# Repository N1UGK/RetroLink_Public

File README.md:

# RetroLink (POTS Telephone Internet Interface)

RetroLink connects a standard POTS (Plain Old Telephone Service) analog telephone to the Internet over Wi-Fi, allowing peer-to-peer calling between devices and retro telephony interfacing.  The RetroLink is intended for private telephone networks in the same building, campus, or even across the globe.  It will not require subscription fees or a third party "app" or platform to use.  The idea came from my daughter (who is 6) asking for a phone to call her friends.  This device can be configured for connecting a close circle of friends or family and using their chosen "phone number" to dial and connect to them.  Any standard "retro" telephone can be plugged into the RetroLink.

## Overview

RetroLink provides a complete, self-contained telephone line interface for real analog telephones (both rotary and DTMF touch-tone). It generates real ringing voltages, provides line battery feed, detects off-hook and on-hook states, digitizes 2-wire voice audio with hardware codecs, and streams bidirectional voice data over Wi-Fi.

## Key Features

- **True POTS Line Interface**: Powered by the **Silvertel Ag1170-S5** SLIC with an onboard DC/DC converter generating -48V loop battery and 65Vrms ringing directly from a 5V supply.
- **Hardware Voice Codec**: **Texas Instruments TLV320AIC1110** providing 8 kHz PCM sampling, companded G.711 µ-law encoding, digital PGA gain control, and programmable sidetone.
- **Microcontroller**: **Raspberry Pi Pico 2 W** (RP2350 with dual ARM Cortex-M33 / Hazard3 RISC-V cores and onboard CYW43 Wi-Fi).
- **Dual-Core Architecture**:
  - **Core 0**: Real-time audio engine with DMA/PIO double buffering, low-latency audio packetization, and SLIC line supervision (hook switch debounce & ring cadence).
  - **Core 1**: CYW43 Wi-Fi stack, lwIP networking, VoIP stream/control protocol, web status interface, and OLED display navigation.
- **User Interface**:
  - 128x64 SSD1306 OLED display via I2C (0x3C)
  - 4-button tactile keypad (Up, Down, OK, Back) via MAX7329 GPIO expander (0x3A)
  - 7 Status LEDs (Off-Hook, MicroSD, Voice Mail, Ringing, Connected, Wi-Fi Link, Error) via MAX7329 (0x38)
- **Local Storage & USB**:
  - MicroSD card slot over SPI0 with FatFS for address books, call logs, and voicemail storage.
  - TinyUSB USB Mass Storage support for mounting the SD card on a PC or Mac.
- **Web Dashboard & Control**:
  - Embedded HTTP server for real-time OLED screen viewing, virtual button control, device status, and network configuration.
- **Secure Firmware Updates**:
  - Dedicated 64 KB custom bootloader with OTP key verification and drag-and-drop UF2 updates over USB.

## Hardware Specifications

| Component | Specification |
|---|---|
| Microcontroller | Raspberry Pi Pico 2 W (RP2350 @ 150MHz) |
| SLIC Module | Silvertel Ag1170-S5 (5V, 600Ω 2-wire impedance) |
| Ring Generator | Onboard Ag1170 ringing (65Vrms @ 20Hz, REN 3 capable) |
| Voice Codec | TI TLV320AIC1110 (PCM / G.711 µ-law, 8 kHz) |
| Display | 0.96" 128x64 I2C OLED (0x3C) |
| I/O Expanders | 2x MAX7329 I2C Expanders (0x38, 0x3A) |
| Power Supply | Single 18650 Li-Ion Cell with BQ24090 Charger & MCP1642B 5V Boost |
| Connector | Standard RJ-11 6P4C Modular Phone Jack |

## Firmware Updates

To update the firmware:
1. Place RetroLink into bootloader mode via the OLED menu: `Settings -> Update Firmware`, or hold the bootsel/startup button combo on power-up.
2. Connect RetroLink to your computer via USB. A mass-storage drive named `RETROLINK` will appear.
3. Drag and drop the latest release `.uf2` file from the `Firmware/` folder onto the drive.
4. The bootloader will verify and flash the image, then automatically reboot into the new firmware.

## Repository Structure

- `Firmware/`: Official firmware release binaries (`.uf2`) and release notes.
- `Hardware/`: 3D CAD STEP models, schematics, and mechanical design files.
- `Documentation/`: User guides, application notes, and reference manuals.
>>>>>>> b99fa2f (Initial commit for RetroLink_Public repository structure)

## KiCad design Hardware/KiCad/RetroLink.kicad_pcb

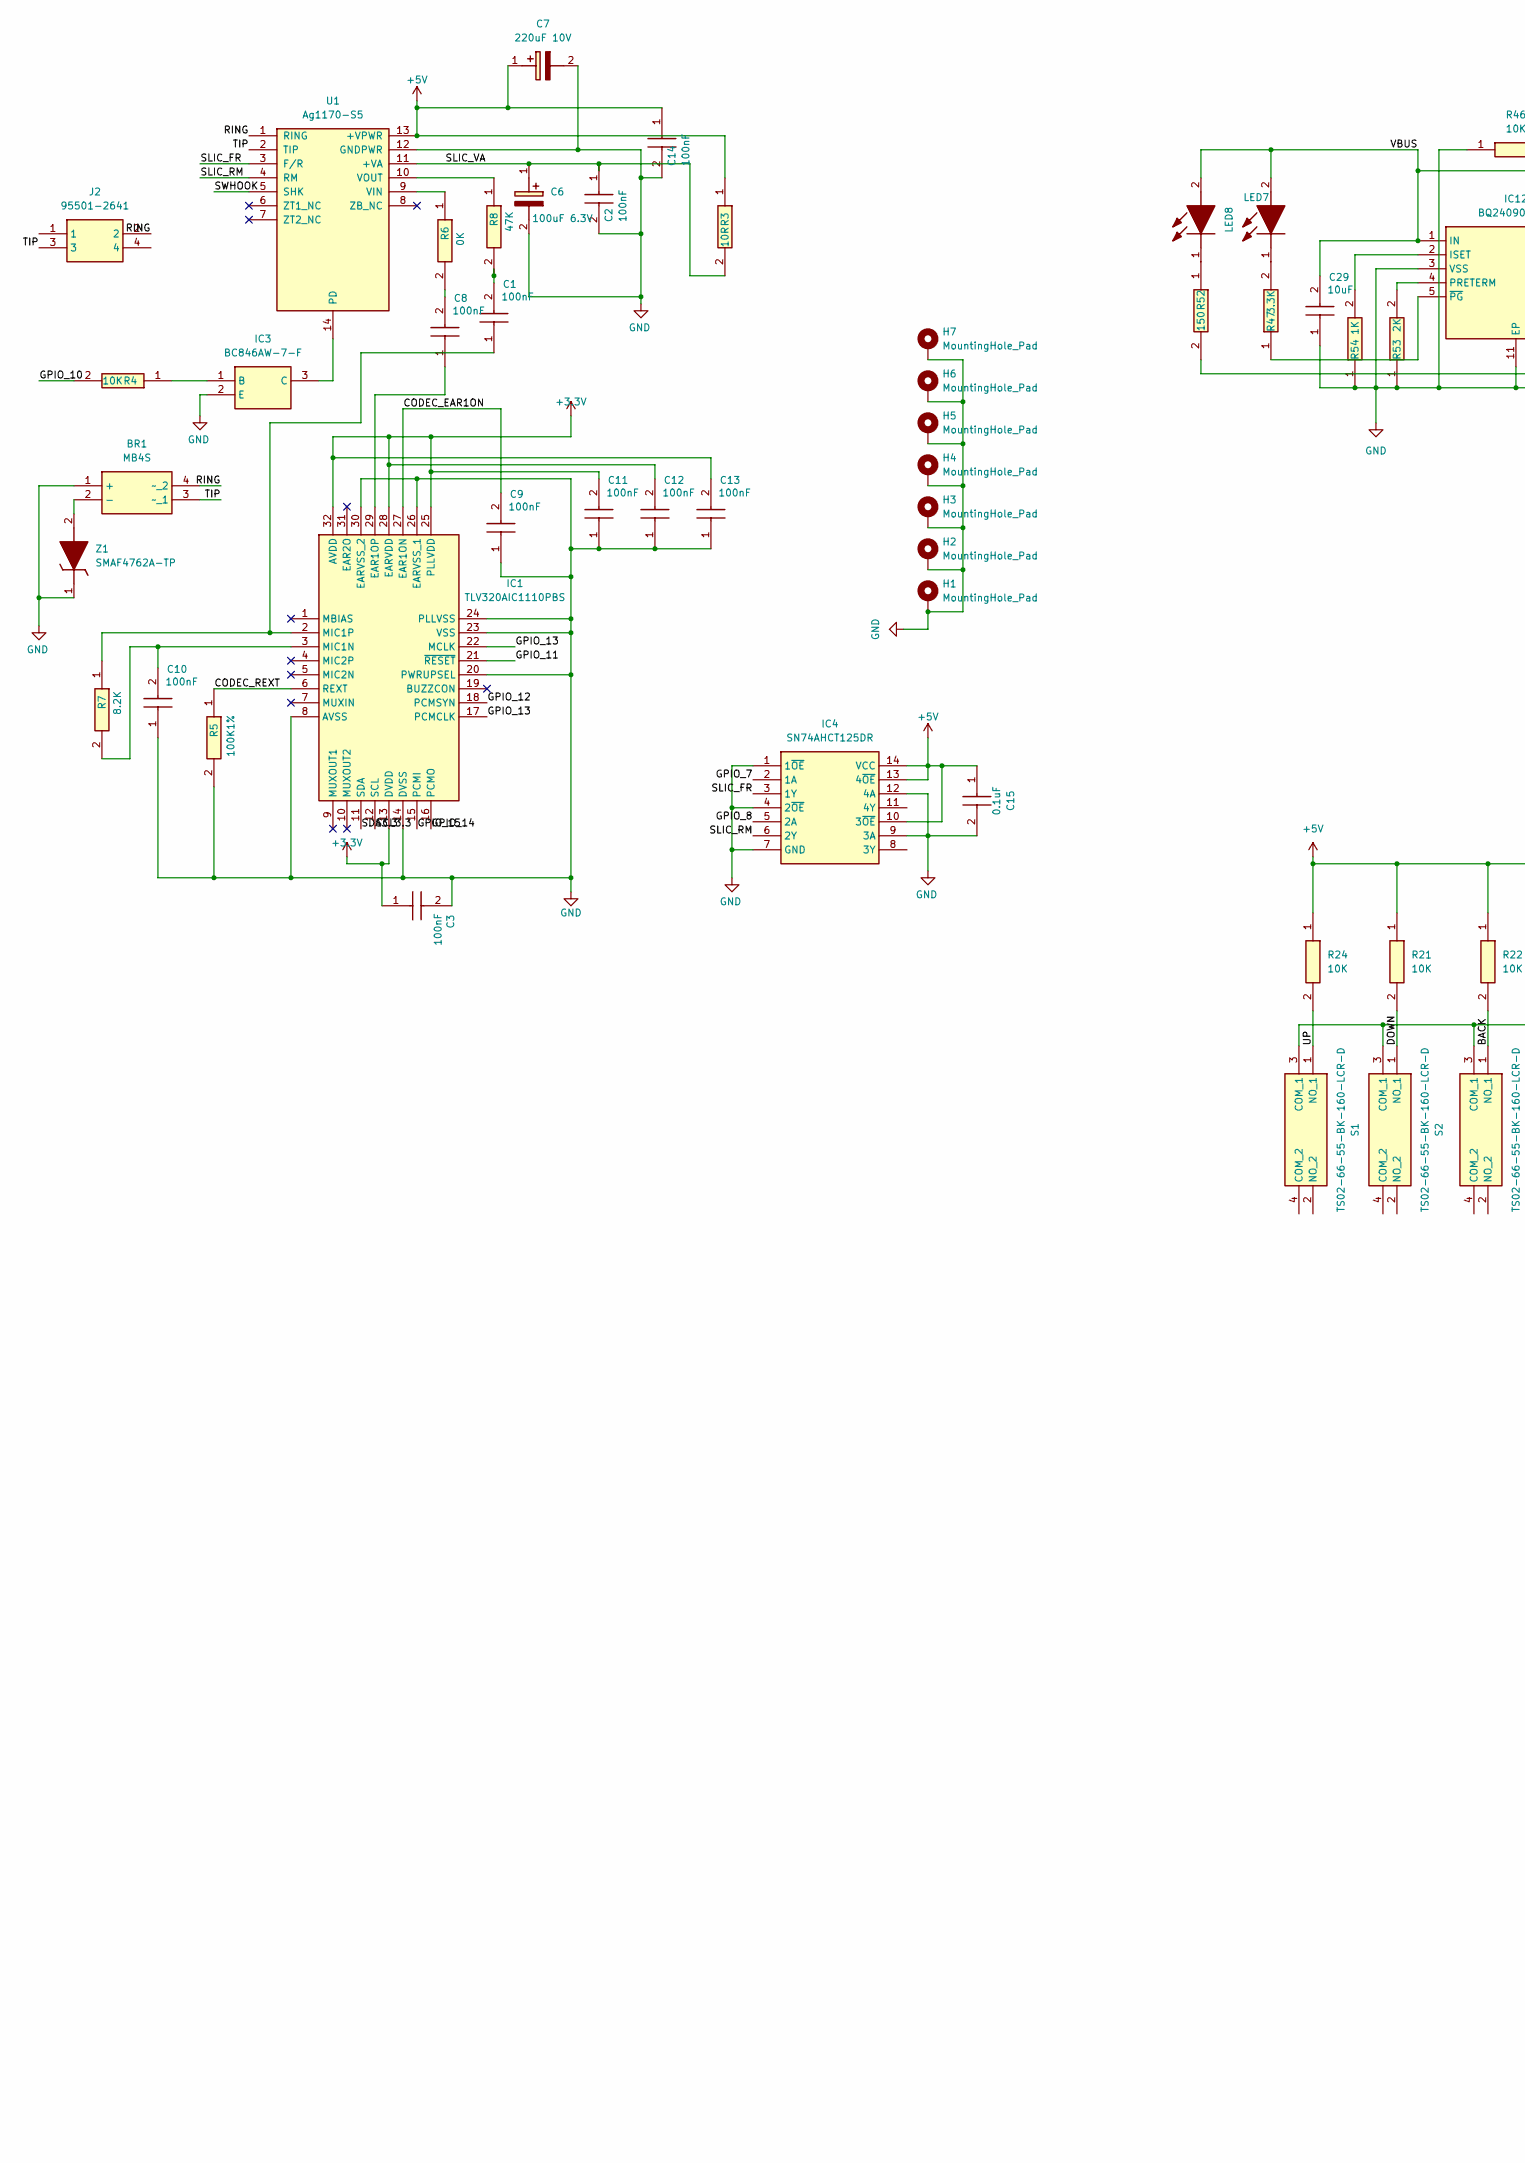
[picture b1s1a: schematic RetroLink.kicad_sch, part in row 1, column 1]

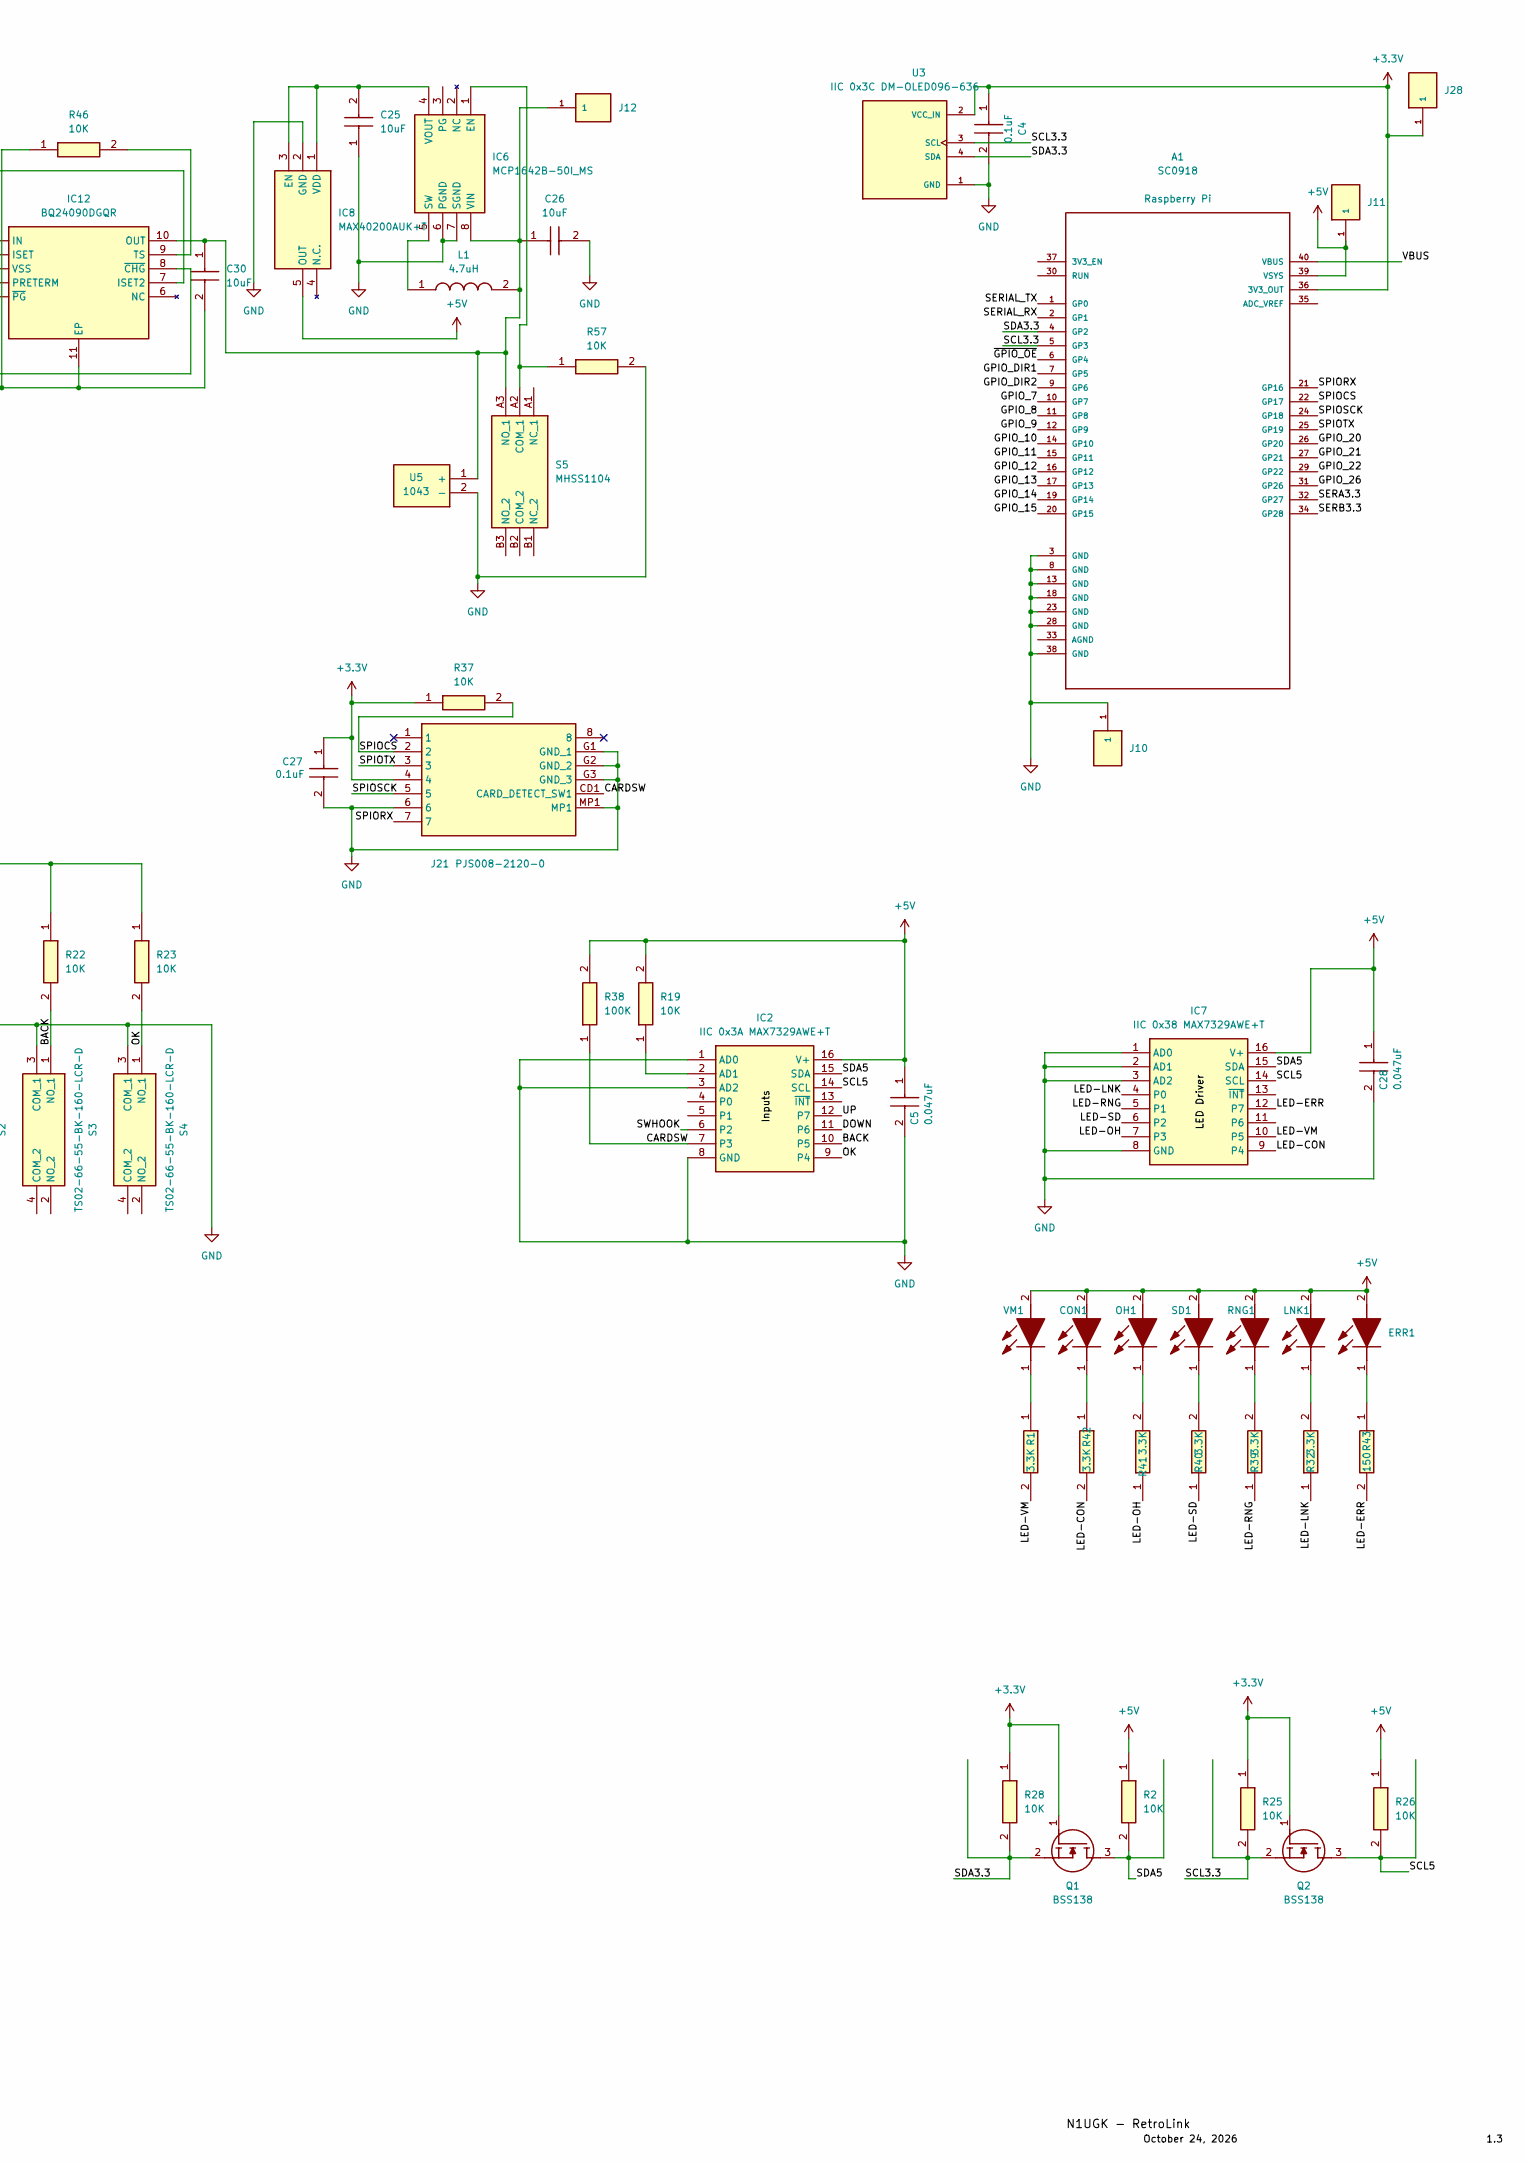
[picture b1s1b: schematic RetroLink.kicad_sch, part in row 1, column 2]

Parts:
A1: SC0918; MODULE_SC0918; PARTREV 1.6
BR1: MB4S; SOP245P670X290-4N; Mouser Part Number 512-MB4S
C1, C3, C8, C9, C10, C11, C12, C13: 100nF; CAPC1608X90N; Mouser Part Number 81-GRM188R60J106ME4D
C2, C14: 100nF; C1206; Mouser Part Number 80-C1206C473J5R
C4, C15: 0.1uF; CAPC3216X229N; Mouser Part Number 581-12063G106ZAT2A
C5, C28: 0.047uF; C1206; Mouser Part Number 80-C1206C473J5R
C6: 100uF 6.3V; CAPPRD200W50D500H1250; Mouser Part Number 80-ESK107M025AC3AA
C7: 220uF 10V; CAPPRD250W50D655H1250; Mouser Part Number 232-16ZLH220MEFC63X1
C25, C26, C29, C30: 10uF; CAPC1608X90N; Mouser Part Number 81-GRM188R60J106ME4D
C27: 0.1uF; CAPC3216X94N; Mouser Part Number 581-12061C103J
CON1: HSMM-A100-S00J1; LEDM3528X200N; Mouser Part Number 630-HSMM-A100-S00J1
ERR1: HSMS-A100-L00J1; HSMSA100L00J1; Mouser Part Number 630-HSMS-A100-L00J1
H1, H2, H3, H4, H5, H6, H7: MountingHole_Pad; MountingHole_3.2mm_M3_Pad_Via
IC1: TLV320AIC1110PBS; QFP50P700X700X120-32N; Mouser Part Number 595-TLV320AIC1110PBS
IC2: IIC 0x3A MAX7329AWE+T; SOIC127P1032X265-16N; Mouser Part Number 700-MAX7329AWET
IC3: BC846AW-7-F; SOT65P210X110-3N; Mouser Part Number 621-BC846AW-7-F
IC4: SN74AHCT125DR; SOIC127P600X175-14N; Mouser Part Number 595-SN74AHCT125DR
IC6: MCP1642B-50I_MS; SOP65P490X110-8N; Mouser Part Number 579-MCP1642B-50I/MS
IC7: IIC 0x38 MAX7329AWE+T; SOIC127P1032X265-16N; Mouser Part Number 700-MAX7329AWET
IC8: MAX40200AUK+T; SOT95P280X145-5N; Mouser Part Number 700-MAX40200AUK+T
IC12: BQ24090DGQR; SOP50P490X110-11N; Mouser Part Number 595-BQ24090DGQR
J2: 95501-2641; 955012641; Mouser Part Number 538-95501-2641
J10, J11, J12, J28: SAMTEC-HMTSW-101-24-X-S-290
J21: PJS008-2120-0; PJS00821200; Mouser Part Number 945-PJS008-2120-0
L1: 4.7uH; EPL3015472MLC; Mouser Part Number 994-EPL3015-472MLC
LED7: HSMM-A100-S00J1; LEDM3528X200N; Mouser Part Number 630-HSMM-A100-S00J1
LED8: HSMS-A100-L00J1; HSMSA100L00J1; Mouser Part Number 630-HSMS-A100-L00J1
LNK1: HSMM-A100-S00J1; LEDM3528X200N; Mouser Part Number 630-HSMM-A100-S00J1
OH1: HSMM-A100-S00J1; LEDM3528X200N; Mouser Part Number 630-HSMM-A100-S00J1
Q1, Q2: BSS138; SOT95P240X120-3N; Mouser Part Number 512-BSS138
R1, R32, R39, R40, R41, R42, R47: 3.3K; RESC2013X65N; Mouser Part Number 756-WCR0805-10KFI
R2, R4, R19, R21, R22, R23, R24, R25, R26, R28, R37, R46, R57: 10K; RESC2013X65N; Mouser Part Number 756-WCR0805-10KFI
R3: 10R; RESC2013X65N; Mouser Part Number 756-WCR0805-10KFI
R5: 100K1%; RESC2013X65N; Mouser Part Number 756-WCR0805-10KFI
R6: 0K; RESC2013X65N; Mouser Part Number 756-WCR0805-10KFI
R7: 8.2K; RESC2013X65N; Mouser Part Number 756-WCR0805-10KFI
R8: 47K; RESC2013X65N; Mouser Part Number 756-WCR0805-10KFI
R38: 100K; RESC2013X65N; Mouser Part Number 756-WCR0805-10KFI
R43, R52: 150; RESC2013X65N; Mouser Part Number 756-WCR0805-10KFI
R53: 2K; RESC2013X65N; Mouser Part Number 756-WCR0805-10KFI
R54: 1K; RESC2013X65N; Mouser Part Number 756-WCR0805-10KFI
RNG1: HSMM-A100-S00J1; LEDM3528X200N; Mouser Part Number 630-HSMM-A100-S00J1
S1, S2, S3, S4: TS02-66-55-BK-160-LCR-D; TS026655BK160LCRD; Mouser Part Number 179-TS026655BK160LCR
S5: MHSS1104; Mouser Part Number 642-MHSS1104
SD1: HSMM-A100-S00J1; LEDM3528X200N; Mouser Part Number 630-HSMM-A100-S00J1
U1: Ag1170-S5
U3: IIC 0x3C DM-OLED096-636; MODULE_DM-OLED096-636; PARTREV 2018-09-10
U5: 1043; Mouser Part Number 534-1043
VM1: HSMM-A100-S00J1; LEDM3528X200N; Mouser Part Number 630-HSMM-A100-S00J1
Z1: SMAF4762A-TP; SODFL5026X125N; Manufacturer_Part_Number SMAF4762A-TP

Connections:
+3.3V: A1.36 (3V3_OUT), C3.1, C4.1, C11.2, C12.2, C13.2, C27.1 (C1), IC1.13 (DVDD), IC1.25 (PLLVDD), IC1.28 (EARVDD), IC1.32 (AVDD), J21.4, J28.1, Q1.1 (G), Q2.1 (G), R25.1, R28.1, R37.1, U3.2 (VCC_IN)
+5V: A1.39 (VSYS), C5.1, C7.1 (+), C14.1, C15.1, C28.1, CON1.2 (A), ERR1.2 (A), IC2.16 (V+), IC4.10 (3~OE), IC4.13 (4~OE), IC4.14 (VCC), IC7.16 (V+), IC8.5 (OUT), J11.1, LNK1.2 (A), OH1.2 (A), R2.1, R3.1, R19.2, R21.1, R22.1, R23.1, R24.1, R26.1, R38.2, RNG1.2 (A), SD1.2 (A), U1.13 (+VPWR), VM1.2 (A)
/BACK: IC2.10 (P5), R22.2, S3.1 (NO_1)
/CARDSW: IC2.7 (P3), J21.CD1 (CARD_DETECT_SW1), R38.1
/CODEC_EAR1ON: C9.2, IC1.27 (EAR1ON)
/CODEC_REXT: IC1.6 (REXT), R5.1
/DOWN: IC2.11 (P6), R21.2, S2.1 (NO_1)
/GPIO_7: A1.10 (GP7), IC4.2 (1A)
/GPIO_8: A1.11 (GP8), IC4.5 (2A)
/GPIO_9: A1.12 (GP9)
/GPIO_10: A1.14 (GP10), R4.2
/GPIO_11: A1.15 (GP11), IC1.21 (~RESET)
/GPIO_12: A1.16 (GP12), IC1.18 (PCMSYN)
/GPIO_13: A1.17 (GP13), IC1.17 (PCMCLK), IC1.22 (MCLK)
/GPIO_14: A1.19 (GP14), IC1.16 (PCMO)
/GPIO_15: A1.20 (GP15), IC1.15 (PCMI)
/GPIO_20: A1.26 (GP20)
/GPIO_21: A1.27 (GP21)
/GPIO_22: A1.29 (GP22)
/GPIO_26: A1.31 (GP26)
/GPIO_DIR1: A1.7 (GP5)
/GPIO_DIR2: A1.9 (GP6)
/LED-CON: IC7.9 (P4), R42.2
/LED-ERR: IC7.12 (P7), R43.2
/LED-LNK: IC7.4 (P0), R32.1
/LED-OH: IC7.7 (P3), R41.1
/LED-RNG: IC7.5 (P1), R39.1
/LED-SD: IC7.6 (P2), R40.1
/LED-VM: IC7.10 (P5), R1.2
/OK: IC2.9 (P4), R23.2, S4.1 (NO_1)
/RING: BR1.4 (~_2), J2.2, U1.1 (RING)
/SCL3.3: A1.5 (GP3), IC1.12 (SCL), Q2.2 (S), R25.2, U3.3 (SCL)
/SCL5: IC2.14 (SCL), IC7.14 (SCL), Q2.3 (D), R26.2
/SDA3.3: A1.4 (GP2), IC1.11 (SDA), Q1.2 (S), R28.2, U3.4 (SDA)
/SDA5: IC2.15 (SDA), IC7.15 (SDA), Q1.3 (D), R2.2
/SERA3.3: A1.32 (GP27)
/SERB3.3: A1.34 (GP28)
/SERIAL_RX: A1.2 (GP1)
/SERIAL_TX: A1.1 (GP0)
/SLIC_FR: IC4.3 (1Y), U1.3 (F/R)
/SLIC_RM: IC4.6 (2Y), U1.4 (RM)
/SLIC_VA: C2.1, C6.1 (+), R3.2, U1.11 (+VA)
/SPIOCS: A1.22 (GP17), J21.2, R37.2
/SPIORX: A1.21 (GP16), J21.7
/SPIOSCK: A1.24 (GP18), J21.5
/SPIOTX: A1.25 (GP19), J21.3
/SWHOOK: IC2.6 (P2), U1.5 (SHK)
/TIP: BR1.3 (~_1), J2.3, U1.2 (TIP)
/UP: IC2.12 (P7), R24.2, S1.1 (NO_1)
/VBUS: A1.40 (VBUS), C29.2, IC12.1 (IN), IC12.7 (ISET2), LED7.2 (A), LED8.2 (A)
/~GPIO_OE: A1.6 (GP4)
GND: A1.3 (GND), A1.8 (GND), A1.13 (GND), A1.18 (GND), A1.23 (GND), A1.28 (GND), A1.38 (GND), BR1.1 (+), C2.2, C3.2, C4.2, C5.2, C6.2 (-), C7.2 (-), C9.1, C10.1, C11.1, C12.1, C13.1, C14.2, C15.2, C25.1, C26.2, C27.2 (C2), C28.2, C29.1, C30.2, H1.1, H2.1, H3.1, H4.1, H5.1, H6.1, H7.1, IC1.8 (AVSS), IC1.14 (DVSS), IC1.20 (PWRUPSEL), IC1.23 (VSS), IC1.24 (PLLVSS), IC1.26 (EARVSS_1), IC1.30 (EARVSS_2), IC2.1 (AD0), IC2.3 (AD2), IC2.8 (GND), IC3.2 (E), IC4.1 (1~OE), IC4.4 (2~OE), IC4.7 (GND), IC4.9 (3A), IC4.12 (4A), IC6.6 (PGND), IC6.7 (SGND), IC7.1 (AD0), IC7.2 (AD1), IC7.3 (AD2), IC7.8 (GND), IC8.2 (GND), IC12.3 (VSS), IC12.11 (EP), J10.1, J21.6, J21.G1 (GND_1), J21.G2 (GND_2), J21.G3 (GND_3), J21.MP1, R5.2, R46.1, R53.1, R54.1, R57.2, S1.3 (COM_1), S2.3 (COM_1), S3.3 (COM_1), S4.3 (COM_1), U1.12 (GNDPWR), U3.1 (GND), U5.2 (-), Z1.1 (K)
unnamed: BR1.2 (-), Z1.2 (A)
unnamed: C1.2, R8.2
unnamed: C8.2, R6.2
unnamed: CON1.1 (K), R42.1
unnamed: ERR1.1 (K), R43.1
unnamed: C8.1, IC1.29 (EAR1OP)
unnamed: C10.2, IC1.3 (MIC1N), R7.2
unnamed: C1.1, IC1.2 (MIC1P), R7.1
unnamed: IC2.2 (AD1), R19.1
unnamed: IC3.1 (B), R4.1
unnamed: IC3.3 (C), U1.14 (PD)
unnamed: IC6.1 (EN), R57.1, S5.A2 (COM_1)
unnamed: IC6.5 (SW), L1.1
unnamed: C25.2, IC6.4 (VOUT), IC8.1 (VDD), IC8.3 (EN)
unnamed: IC12.2 (ISET), R54.2
unnamed: C26.1, C30.1, IC6.8 (VIN), IC12.10 (OUT), J12.1, L1.2, S5.A3 (NO_1), U5.1 (+)
unnamed: IC12.4 (PRETERM), R53.2
unnamed: IC12.9 (TS), R46.2
unnamed: IC12.8 (~CHG), R52.2
unnamed: IC12.5 (~PG), R47.1
unnamed: LED7.1 (K), R47.2
unnamed: LED8.1 (K), R52.1
unnamed: LNK1.1 (K), R32.2
unnamed: OH1.1 (K), R41.2
unnamed: R39.2, RNG1.1 (K)
unnamed: R40.2, SD1.1 (K)
unnamed: R6.1, U1.9 (VIN)
unnamed: R8.1, U1.10 (VOUT)
unnamed: R1.1, VM1.1 (K)

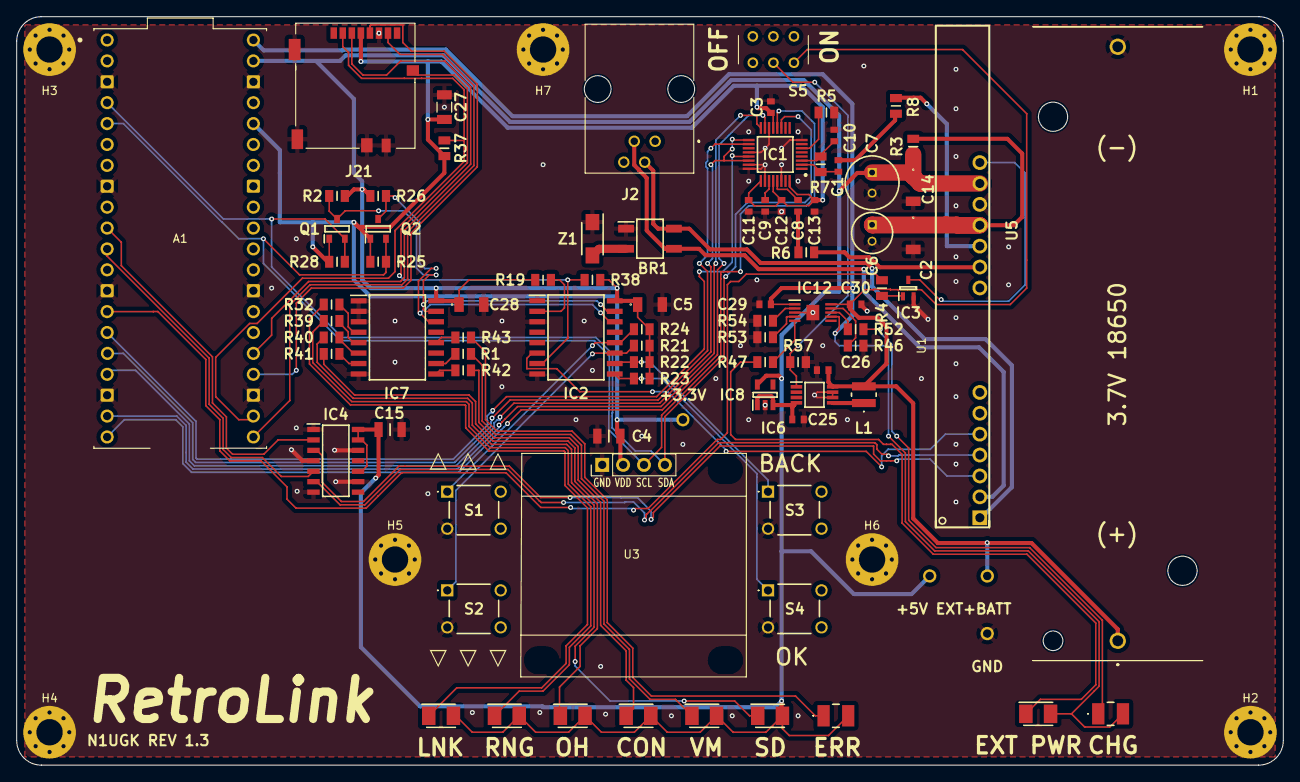
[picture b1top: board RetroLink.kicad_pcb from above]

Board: 2 copper layers, 154.0 x 91.0 mm, 95 parts (0 on the bottom side), 69 nets.
